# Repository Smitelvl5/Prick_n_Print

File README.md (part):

# Print-n-Prick

An IoT system that pairs a thermal receipt printer with a hand sanitizer dispenser, controlled remotely through an HTTP backend. Send messages from your phone and they print on thermal paper along with live weather and sensor data. A secondary display module provides a touchscreen GUI, web dashboard, and real-time sensor monitoring.

## HTTP backend

The TZT display polls your web server for commands, audio, and images. You run the included Flask server (or your own) and POST commands to it; the ESP32 polls `/api/commands`, `/api/audio`, and `/api/images`.

**Configure:** In **`include/config_tzt.h`** set **`BACKEND_URL`** to your server (e.g. `"http://192.168.1.100:5000"`). See [BACKEND_HTTP.md](BACKEND_HTTP.md) for setup and usage.

| What you send | What the TZT does |
|---------------|-------------------|
| **Text message** | Prints it (via Main ESP32), saves it to SD (`/data/messages/`), and shows it on the TZT screen. |
| **Audio** | Saves it to SD (`/data/audio/`) and plays it on the TZT. You can send a **URL** (TZT downloads and saves) or a **filename** (play a file already on SD). |
| **Image** | Saves it to SD (`/data/images/`) and shows it on the TZT. You can send a **URL** (TZT downloads and saves) or a **filename** (show a file already on SD). |

**Command types** (POST to your backend; see `raspberrypi/README.md` for the API):

- **`print`** – Text message (`type`, `data`, optional `source`)
- **`download_audio`** – Download audio from URL, save to SD, and play
- **`play_audio`** – Play a file already on SD
- **`download_image`** – Download image from URL, save to SD, and show
- **`show_image`** – Show a file already on SD

Pump/LED and other hardware control use the TZT’s web UI or HTTP API on port 8080.

---

## Architecture

The system is built on **two ESP32 modules** connected over ESP-NOW:

| | Main ESP32 (WROOM-32) | TZT Display ESP32 (CYD) |
|---|---|---|
| **Role** | Hardware controller | Brain / UI / cloud |
| **PlatformIO env** | `esp32-wroom-32` | `tzt-esp32-devkit` |
| **Serial port** | COM3 (CH340C on the main PCB) | COM7 (CH340) |
| **Controls** | Printer, pump, LED, sensors | 2.4" TFT + touch, web server, HTTP backend, SD card, speaker |
| **Network** | WiFi (for ESP-NOW channel sync) | WiFi + HTTP backend + HTTP server (port 8080) |
| **Config file** | `include/config.h` | `include/config_tzt.h` |

```
                 ┌──────────────────┐
  iOS Shortcut ──┤                  │
  Python script ─┤  HTTP backend    │
  Web UI (POST) ─┤  /api/commands   │
                 └────────┬─────────┘
                          │ poll (10-30 s)
                          ▼
              ┌──────────────────────────┐
              │   TZT Display ESP32     │
              │   (CYD 2.4" ILI9341)    │
              │                          │
              │  ● Web server :8080     │
              │  ● HTTP backend client  │
              │  ● LVGL touchscreen GUI │
              │  ● Reminder scheduler    │
              │  ● Grocery / Todo lists  │
              │  ● SD card (FAT32)       │
              │  ● Speaker (GPIO26 DAC)  │
              └────────────┬─────────────┘
                           │ ESP-NOW
                           ▼
              ┌──────────────────────────┐
              │   Main ESP32 (WROOM-32)  │
              │                          │
              │  ● Thermal printer       │
              │  ● Sanitizer pump        │
              │  ● 12 V LED (PWM)        │
              │  ● IR motion sensor      │
              │  ● Moisture sensor       │
              │  ● Light sensor (LM393)  │
              │  ● Sends sensor data     │
              │    back via ESP-NOW      │
              └──────────────────────────┘
```

### Message Flow

1. User sends message (iOS Shortcut, Python script, or web UI) to the HTTP backend
2. Message is POSTed to the backend (e.g. `/api/commands`)
3. TZT polls the backend every ~10–30 s, fetches new commands
4. TZT sends print command to Main ESP32 over ESP-NOW (chunked if > 199 bytes)
5. Main ESP32 assembles message, fetches weather, reads sensors, prints receipt
6. TZT marks the command as processed (backend may delete or mark it)

### Sensor Data Flow

1. Main ESP32 reads sensors every 2 seconds
2. Sends `SensorDataPacket` to TZT over ESP-NOW every 10 seconds
3. TZT updates the LVGL display and caches data for the web dashboard

---

## Quick Start

### Prerequisites

- [PlatformIO](https://platformio.org/) (CLI or VS Code extension)
- USB data cable for each ESP32
- HTTP backend server (see [BACKEND_HTTP.md](BACKEND_HTTP.md); optional for basic testing)

### 1. Set MAC Addresses

Each board prints its MAC address on boot over serial. Copy them into the config files:

- Main ESP32's MAC goes into TZT's own config, `include/config_tzt.h`, as `MAIN_ESP32_MAC_ADDRESS`
- TZT Display's MAC goes into Main's own config, `include/config.h`, as `TZT_DISPLAY_MAC_ADDRESS`

Format: `{0xAA, 0xBB, 0xCC, 0xDD, 0xEE, 0xFF}`

### 2. Build and Flash

```bash
# Main ESP32 (COM3)
pio run -e esp32-wroom-32 -t upload -t monitor

# TZT Display (COM7)
pio run -e tzt-esp32-devkit -t upload -t monitor
```

### 3. Connect to WiFi

On first boot each board creates a WiFi access point for configuration:

| Board | AP SSID | AP Password | Portal URL |
|---|---|---|---|
| Main ESP32 | `Print-n-Prick` | `your-portal-password` | `http://192.168.4.1` |
| TZT Display | `TZT_Display` | `your-portal-password` | `http://192.168.4.1` |

Connect to each AP, open the portal, and enter your home WiFi credentials. The boards save them and reconnect automatically on future boots.

### 4. Access the Web Dashboard

Once TZT is on your WiFi, find its IP in the serial monitor and open:

```
http://<TZT-IP>:8080
```

Password: `your-web-password` (set via `WEB_PASSWORD` in `secrets.h`)

---

## Hardware

### Main ESP32 (WROOM-32)

The Main ESP32 lives on a custom PCB (see [Main PCB](#main-pcb)) that replaces the old ESP32 DevKit, its breakout board and the separate LM2596 PSU board. The firmware pin map is unchanged.

#### Pin Map

| GPIO | Function | Direction | Component |
|------|----------|-----------|-----------|
| 2 | Status LED | Output | On-board LED D42 (active HIGH) |
| 16 | Serial RX2 | Input | Thermal printer data (J11), 1 k + clamp diode |
| 17 | Serial TX2 | Output | Thermal printer data (J11), 100 Ω series |
| 26 | Pump control | Output | AO3400A low-side MOSFET (J63) |
| 27 | LED PWM | Output | AO3400A low-side MOSFET, 12 V LED (J60) |
| 32 | IR sensor | Input | J12, 1 k + clamp to 3.3 V (sensor runs on 5 V) |
| 34 | Moisture sensor | ADC Input | J13, 1 k + 100 nF filter |
| 35 | Light sensor | ADC Input | J14, 1 k + 100 nF filter |

> GPIO 34 and 35 are input-only pins (no internal pull-ups). GPIO 16/17 are used for the thermal printer's Serial2 UART. GPIO 4, 13, 14, 18, 19, 21, 22, 23, 25 and 33 are spare and broken out on the J20 expansion header.

#### Components

| Device | Supply | Connector | Notes |
|---|---|---|---|
| **Thermal Printer** -- QR204 | 9 V (5-9 V), ~2 A peak | J61 power, J11 data | 9600 baud, Serial2. The firmware never reads from the printer, so leave the printer's TX wire (J11 pin 3) unconnected; on RS-232 models it swings negative. |
| **Sanitizer Pump** -- CJWP08 micro diaphragm | **3.3 V** | J63 | Voltage set by solder jumper JP1: bridge **1-2 for 3.3 V** (2-3 = 5 V would overdrive a 3.3 V pump). JP1 ships open. |
| **12 V LED** -- 5 W | 12 V, ~0.42 A | J60 | PWM dimming, software ramp (1 V/s), 1.1 A PTC |
| **IR Sensor** | **5 V** | J12 | Digital, active LOW = detected. Fed through its own 0.2 A PTC (F52); its output is clamped to 3.3 V before GPIO32 |
| **Moisture Sensor** -- capacitive | 3.3 V | J13 | Analog 0-4095 mapped to 0-100% |
| **Light Sensor** -- LM393 module | 3.3 V | J14 | Analog output, potentiometer for sensitivity tuning |
| **TZT Display** (CYD) | 5 V | J62 | 1.1 A PTC |

The moisture and light sensors share a 0.2 A PTC (F50) on 3.3 V, so their outputs can never exceed the ESP32's 3.3 V input limit.

### TZT Display ESP32 (CYD -- Cheap Yellow Display)

The TZT module is an [ESP32 Cheap Yellow Display](https://github.com/witnessmenow/ESP32-Cheap-Yellow-Display) -- a single board with an integrated 2.4" ILI9341 TFT, XPT2046 resistive touch controller, micro SD card slot, speaker amplifier, and RGB LED.

#### Pin Map (Fixed by PCB)

**Display (HSPI):**

| GPIO | Function |
|------|----------|
| 2 | TFT DC (data/command) |
| 12 | TFT MISO |
| 13 | TFT MOSI |
| 14 | TFT SCLK |
| 15 | TFT CS |
| 27 | TFT backlight |

**Touch (shared HSPI):**

| GPIO | Function |
|------|----------|
| 33 | XPT2046 CS |
| 25 | XPT2046 CLK |
| 32 | XPT2046 MOSI |
| 36 | XPT2046 IRQ |
| 39 | XPT2046 MISO |

**SD Card (VSPI):**

| GPIO | Function |
|------|----------|
| 5 | SD CS |
| 18 | SD SCK |
| 19 | SD MISO |
| 23 | SD MOSI |

**Peripherals:**

| GPIO | Function |
|------|----------|
| 4 | RGB LED -- Red |
| 16 | RGB LED -- Green |
| 17 | RGB LED -- Blue |
| 26 | Speaker (DAC channel 2, onboard amp) |
| 34 | LDR (light-dependent resistor) |

**Connectors:**

| Label | Type | Pins | Use |
|-------|------|------|-----|
| P1 | 4-pin 1.25 mm JST | VIN, TX, RX, GND | Serial |
| P3 | 4-pin 1.25 mm JST | GND, IO35, IO22, IO21 | GPIO |
| P4 | 2-pin 1.25 mm JST | Speaker +/- | Speaker output |
| CN1 | 4-pin 1.25 mm JST | GND, IO22, IO27, 3.3V | GPIO / I2C |

> Reference: [CYD Pin Documentation](https://github.com/witnessmenow/ESP32-Cheap-Yellow-Display/blob/main/PINS.md)

#### LVGL Screens

The touchscreen GUI has a bottom navigation bar with four tabs, plus a persistent status bar (time/IP/WiFi SSID):

1. **Home** -- latest printed message, quick status, and a button into message history (SD card)
2. **Sensors** -- live moisture, sanitizer, LED, and pump status from the Main ESP32 (read-only)
3. **Media** -- Photo/Audio sub-tab toggle: browse and play received images/audio, reminders, groceries, and todos
4. **Settings** -- WiFi SSID display, volume control, and device configuration

---

## ESP-NOW Protocol

The two boards communicate over ESP-NOW, a low-latency peer-to-peer protocol that works alongside WiFi.

### Packet Types

| Type | ID | Direction | Purpose |
|------|----|-----------|---------|
| `SENSOR_DATA` | 0x01 | Main -> TZT | Sensor readings (moisture, light, IR, LED, pump) |
| `COMMAND` | 0x02 | TZT -> Main | Hardware commands (print, pump, LED, settings) |
| `ACK` | 0x03 | Both | Acknowledgment with sequence number |
| `STATUS_REQUEST` | 0x04 | TZT -> Main | Request immediate sensor data |
| `CHUNK_ACK` | 0x05 | Main -> TZT | Acknowledge receipt of a print chunk |

### Command Types

| Command | ID | Description |
|---------|----|-------------|
| `CMD_PRINT` | 0x01 | Print message (up to 200 bytes) |
| `CMD_DISPENSE_START` | 0x02 | Start pump |
| `CMD_DISPENSE_STOP` | 0x03 | Stop pump |
| `CMD_RESET_SANITIZER` | 0x04 | Reset sanitizer level to 100% |
| `CMD_SET_LED_BRIGHTNESS` | 0x05 | Set LED (param1 = 0-255) |
| `CMD_SET_AUTO_BRIGHTNESS` | 0x07 | Toggle auto-brightness (param1 = 0/1) |
| `CMD_SET_AUTO_DISPENSE` | 0x0D | Toggle auto-dispense (param1 = 0/1) |
| `CMD_PRINT_CHUNK_START` | 0x10 | Begin chunked print (param2 = total chunks) |
| `CMD_PRINT_CHUNK` | 0x0F | One chunk of a long message (param1 = index) |

### Chunked Printing

Messages longer than 199 bytes are split into chunks:

1. TZT sends `CMD_PRINT_CHUNK_START` with the total chunk count
2. TZT sends the first `CMD_PRINT_CHUNK`
3. Main acknowledges with `CHUNK_ACK`
4. TZT sends the next chunk; repeat until done
5. Main assembles the full message and prints

Timeout: 15 seconds per chunk. Retry: 2 seconds. Max payload: ~25 KB (128 chunks x 199 bytes).

### Reliability

- XOR checksums on every packet
- Sequence numbers for ACK matching
- Automatic retry on send failure (2-3 attempts)
- Collision avoidance: 700 ms quiet period after receiving sensor data before sending commands
- Duplicate detection: Main deduplicates repeated settings commands within 1 second

---

## Web Dashboard

The TZT Display hosts a web server on port 8080 with a mobile-optimized dashboard.

### Authentication

- Password: `your-web-password` (set via `WEB_PASSWORD` in `secrets.h`)
- Session tokens valid for 1 hour (cookie-based)

### Sections

- **Sensor Status** -- Moisture, sanitizer level, light, IR, LED brightness, pump state (read-only; live data from the Main ESP32 over ESP-NOW)
- **Reminders** -- Schedule messages to print at a future time (presets: 1 min to 1 week)
- **Grocery List** -- Add items, print the list, clear all
- **Todo List** -- Add items, print the list, clear all
- **Hardware Diagnostics** -- Read sensors, send a test message through the full print pipeline (SD save -> ESP-NOW -> Main prints)

> Pump/LED testing and hardware settings (duration, cooldown, calibration, auto-dispense, auto-brightness) live only on the **Main ESP32's test server** (`http://<Main-ESP32-IP>:8081`) -- see [Hardware Testing](#hardware-testing) below. They used to be duplicated here and on the TZT, which let the two boards fight over settings on every TZT boot; now there's a single place that owns them.

### API Endpoints

| Method | Path | Description |
|--------|------|-------------|
| GET | `/api/login` | Shortcut-friendly login (session cookie) |
| GET | `/api/status` | Sensor readings |
| POST | `/api/reset-sanitizer` | Reset sanitizer to 100% |
| POST | `/api/test/send-message` | Send a test message through the full print pipeline |
| POST | `/api/test/play-audio` | Play an audio file already on SD |
| POST | `/api/test/show-image` | Show an image file already on SD |
| GET/POST | `/api/reminders` | List or add reminders |
| DELETE | `/api/reminders/{id}` | Delete a reminder |
| GET/POST | `/api/groceries` | List or add grocery items |
| DELETE | `/api/groceries` | Clear grocery list |
| POST | `/api/groceries/print` | Print grocery list |
| GET/POST | `/api/todos` | List or add todo items |
| DELETE | `/api/todos` | Clear todo list |
| POST | `/api/todos/print` | Print todo list |

Pump/LED/printer hardware control, tests, and settings are not on this server -- see [Hardware Testing](#hardware-testing) for the Main ESP32's own test server.

---

## Remote Messaging

### iOS Shortcuts

Create a shortcut with these four actions:

1. **Ask for Input** -- Question: "Your message:", type: Text, allow multiple lines
2. **Text** -- Paste the JSON template below, replacing the placeholder with the Provided Input variable:

```json
{
  "type": "print",
  "data": "[Provided Input]",
  "processed": false
}
```

3. **Get Contents of URL**
   - URL: `http://<YOUR-BACKEND-URL>/api/commands` (e.g. `http://192.168.1.100:5000/api/commands`)
   - Method: POST
   - Headers: `Content-Type: application/json`
   - Request Body: **File** (select the Text from step 2)

4. **Show Notification** -- "Message sent!"

> Use `"source": "web"` in the JSON to print the message alone (no header/weather). Omit `source` or use `"source": "shortcut"` for a full receipt with weather and sensor data.

### Python Script

```bash
python scripts/post_to_backend.py --url http://YOUR_SERVER_IP:5000 --message "Your message here"
```

### Print Formats

**Full receipt** (Shortcut / no source):

```
================================
     SMIT'S MESSAGE
================================
Date: Feb 17, 2026 02:30 PM

Your message text here

--------------------------------
Today's Weather:
  Partly Cloudy, 52 F

Moisture: 45.2%  Sanitizer: 78%
================================
```

**Message-only** (Web UI / `"source": "web"`):

```
Your message text here
```

---

## Hardware Testing

### Main ESP32 Test Server

The Main ESP32 runs an HTTP test server on **port 8081** (`http://<Main-ESP32-IP>:8081`) -- open it in a browser for a bench-test panel, or hit the routes directly with curl. This is the **only** place hardware is tested or reconfigured; the TZT dashboard's old duplicate controls (and its boot-time settings push over ESP-NOW) were removed so the two boards can no longer fight over pump/LED settings.

| Route | Description |
|-------|-------------|
| GET `/` | Bench-test web panel |
| GET `/status` | Live hardware status (JSON) |
| GET `/sensors` | Read moisture/IR/light now |
| GET `/printer/test` | Printer test pattern |
| GET `/printer/raw` | Raw test line |
| GET `/printer/receipt` | Sample receipt |
| GET `/printer/feed?lines=N` | Feed N lines |
| GET `/pump?ms=N` | Run pump for N ms (max 5000) |
| GET `/led?level=N&ms=N` | Set LED level (0-255) for N ms |
| GET `/settings` | Get pump duration/cooldown, auto-dispense, auto-brightness |
| GET `/settings/pump-duration?ms=N` | Set max pump dispense duration |
| GET `/settings/pump-cooldown?ms=N` | Set pump cooldown between dispenses |
| GET `/settings/auto-dispense?enabled=0\|1` | Toggle IR-sensor-triggers-pump |
| GET `/settings/auto-brightness?enabled=0\|1` | Toggle LED-follows-light-sensor |
| GET `/settings/light-calibration?point=min\|max` | Record current light reading as the dark/bright calibration point |

### TZT Display -- Touch Calibration

The current `TOUCH_AX`-`TOUCH_CY` coefficients in `config_tzt.h` were captured from a one-off calibration sketch that is no longer part of this repo. If the touchscreen needs recalibrating on different hardware, write a small sketch using `TFT_eSPI`'s built-in `calibrateTouch()` and paste the resulting coefficients into `config_tzt.h`.

---

## Project Structure

```
Prick_n_Print/
├── include/
│   ├── config.h              # Main ESP32 configuration (pins, timing, WiFi, ESP-NOW)
│   ├── config_tzt.h          # TZT Display configuration (display, WiFi, HTTP backend, ESP-NOW)
│   ├── User_Setup.h          # TFT_eSPI pin definitions (copied into library at build time)
│   ├── lv_conf.h             # LVGL configuration
│   ├── HardwareAbstraction.h # Hardware abstraction layer
│   ├── TestServer.h          # Bench-test HTTP server (port 8081) - hardware tests & settings
│   ├── PrinterService.h      # Thermal printer service
│   ├── HttpBackendService.h  # HTTP backend client
│   ├── ReminderService.h     # Reminder scheduler
│   └── Logger.h              # Serial logging
├── src/
│   ├── main.cpp              # Main ESP32 entry point
│   ├── HardwareAbstraction.cpp
│   ├── TestServer.cpp        # Bench-test HTTP server (port 8081) - hardware tests & settings
│   ├── PrinterService.cpp
│   ├── Logger.cpp
│   └── tzt-display/
│       └── main.cpp          # TZT Display entry point (web server, HTTP backend, LVGL, ESP-NOW)
├── raspberrypi/
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
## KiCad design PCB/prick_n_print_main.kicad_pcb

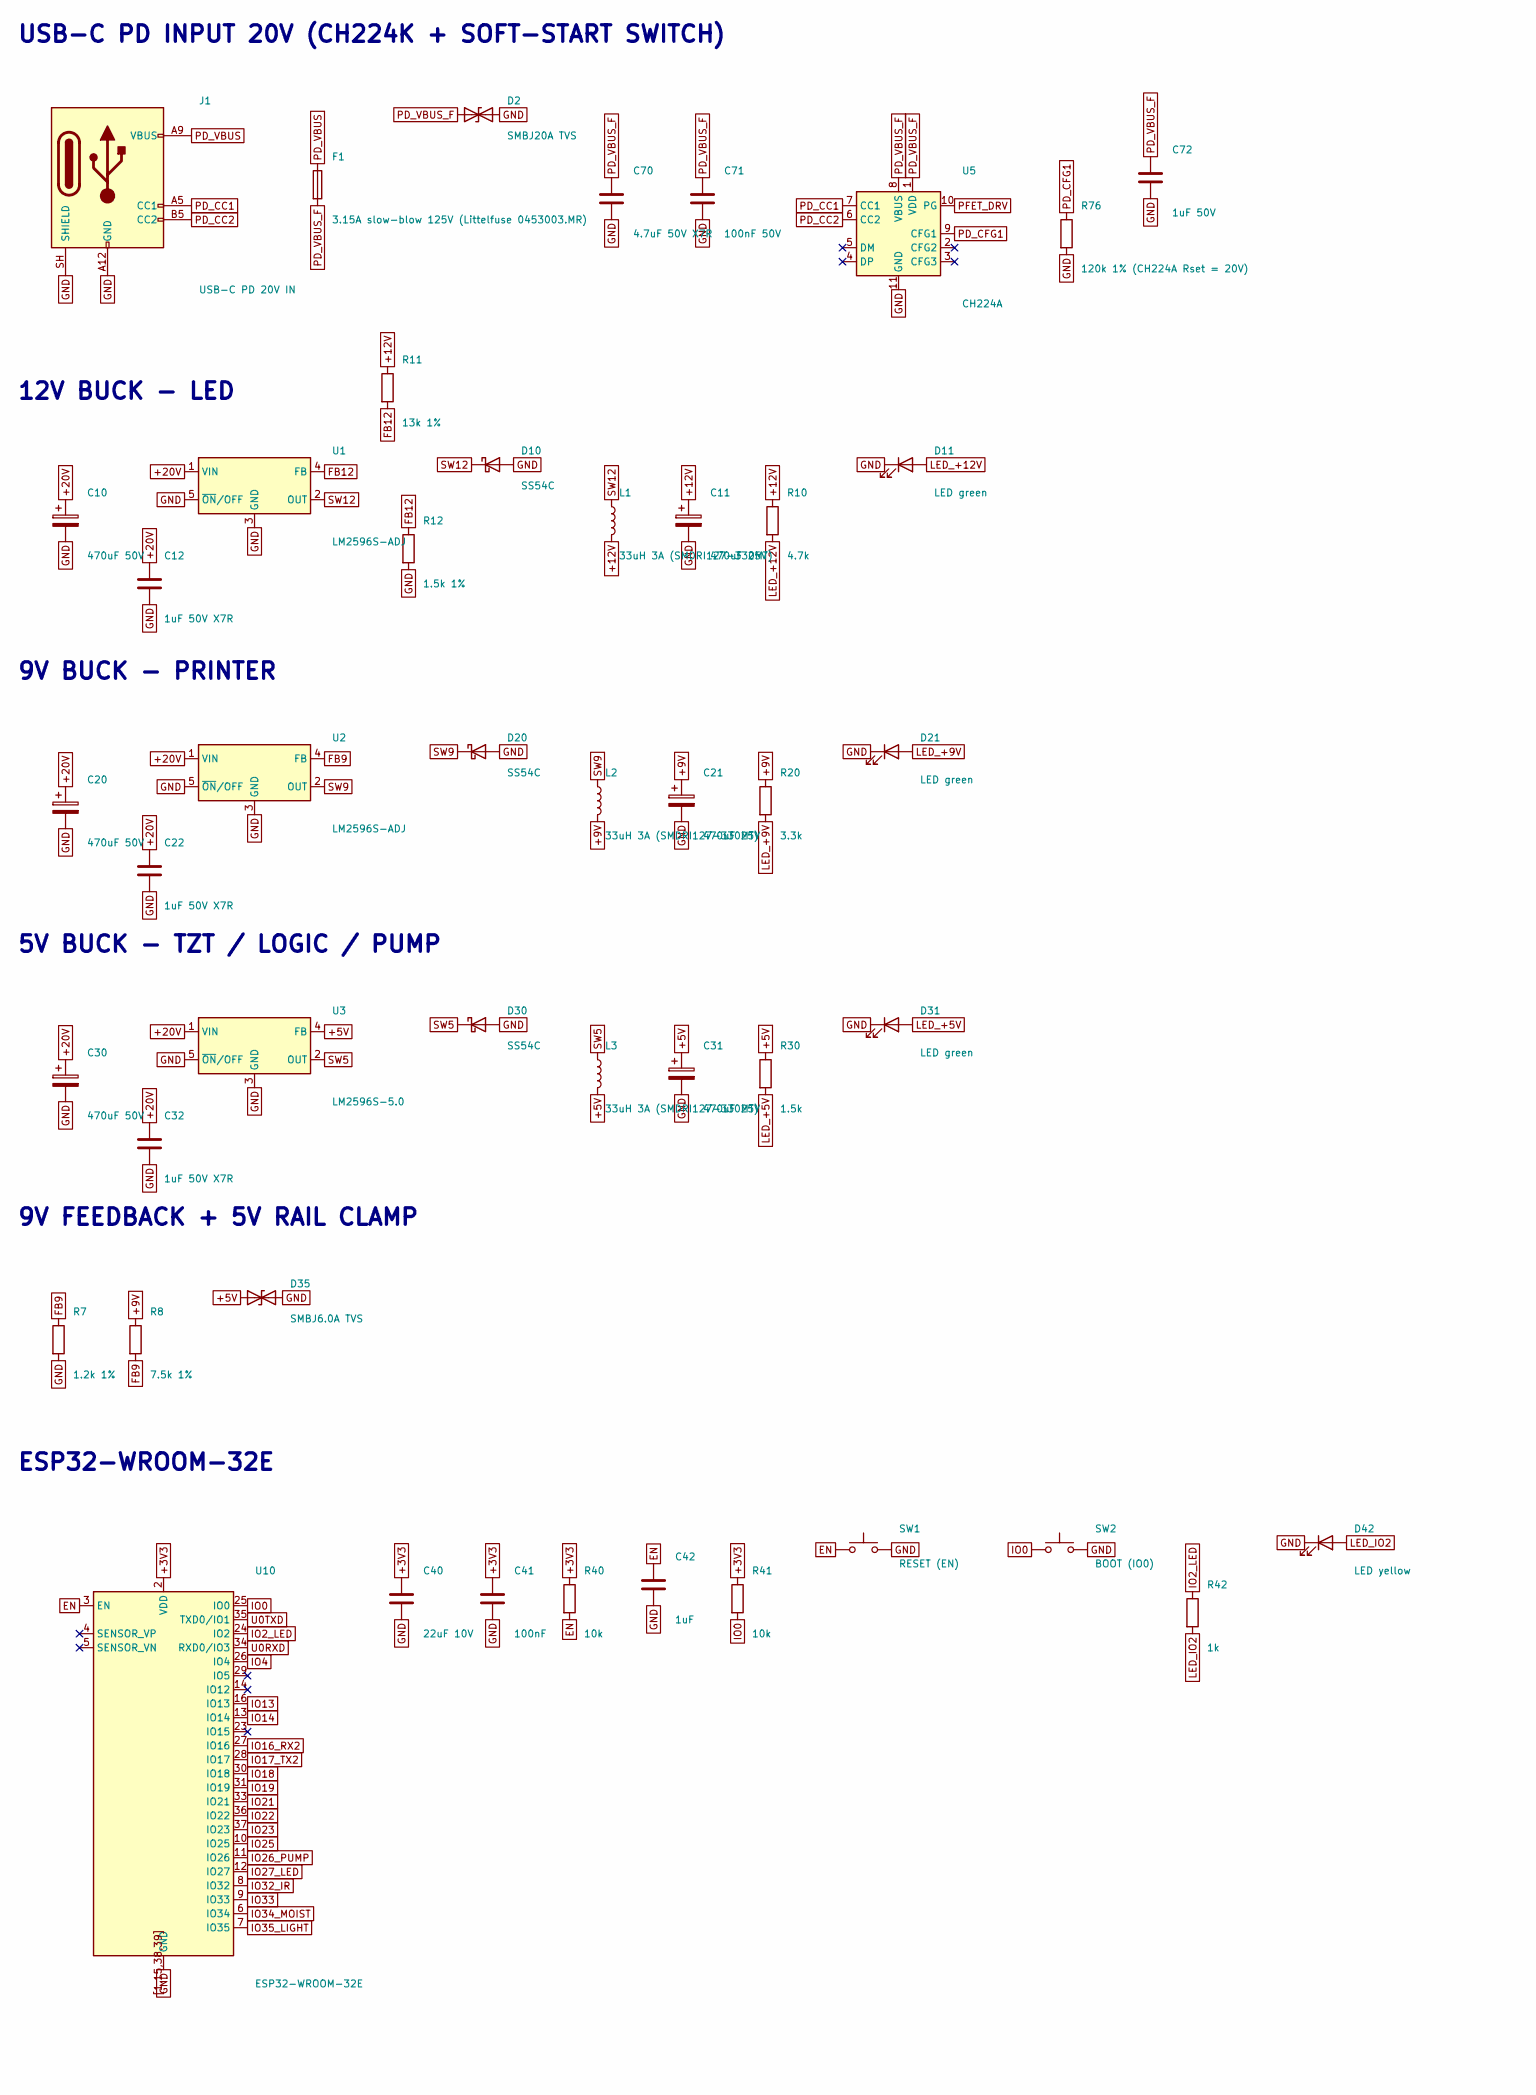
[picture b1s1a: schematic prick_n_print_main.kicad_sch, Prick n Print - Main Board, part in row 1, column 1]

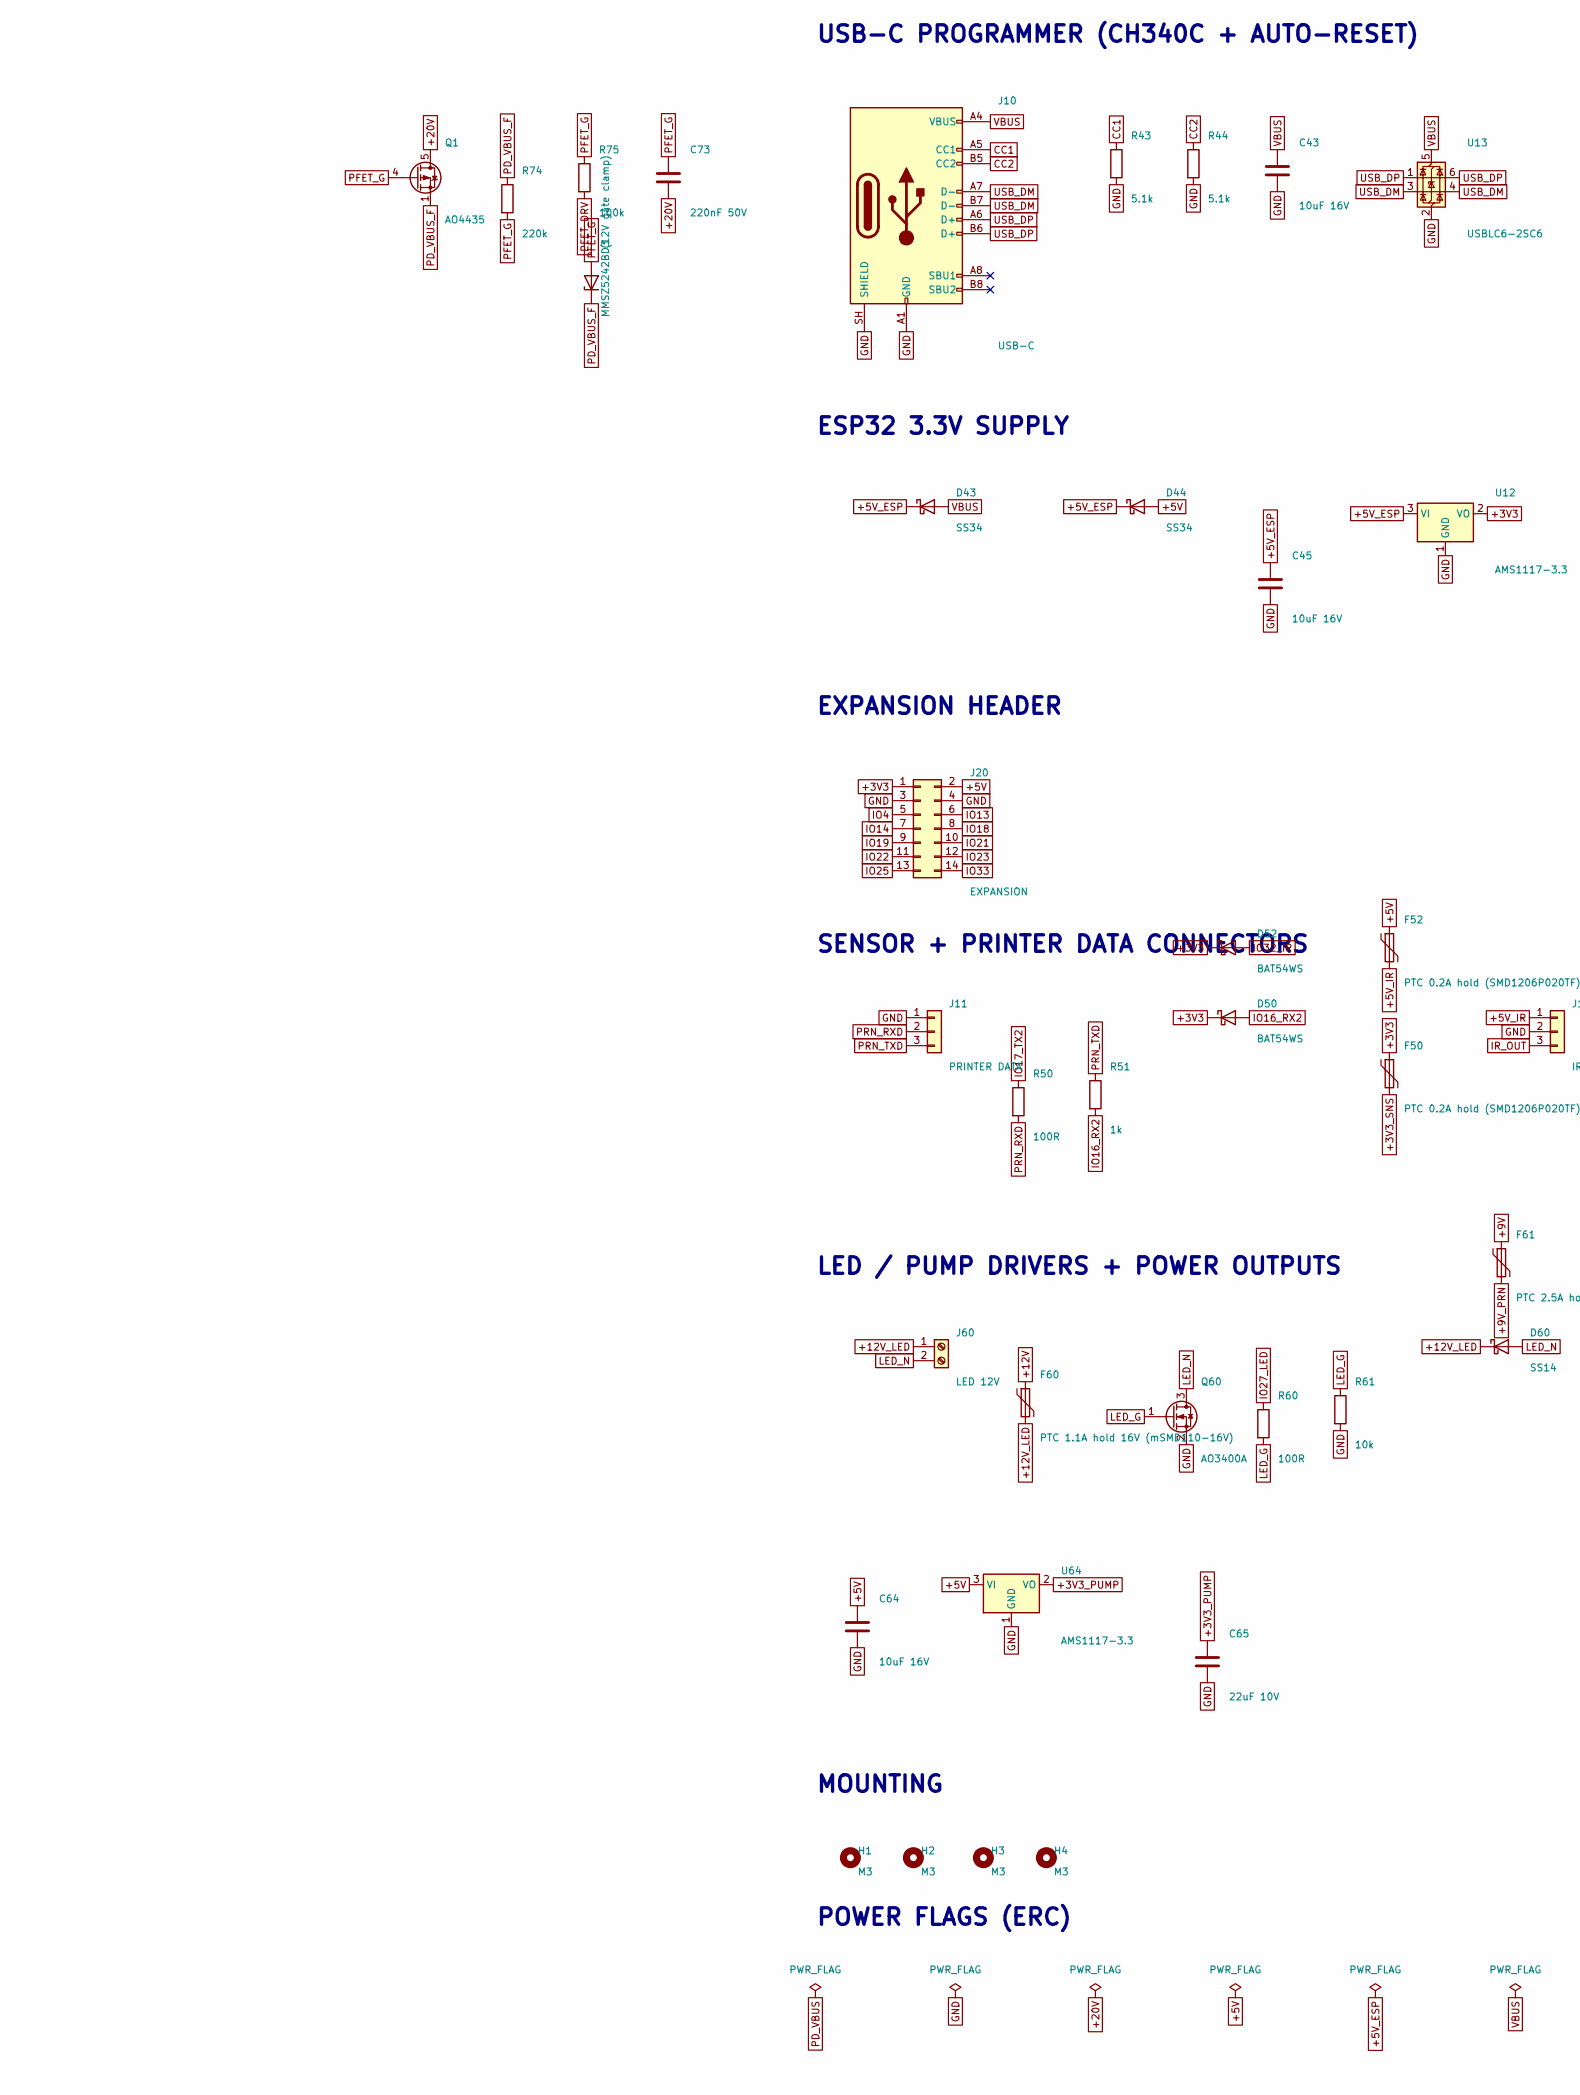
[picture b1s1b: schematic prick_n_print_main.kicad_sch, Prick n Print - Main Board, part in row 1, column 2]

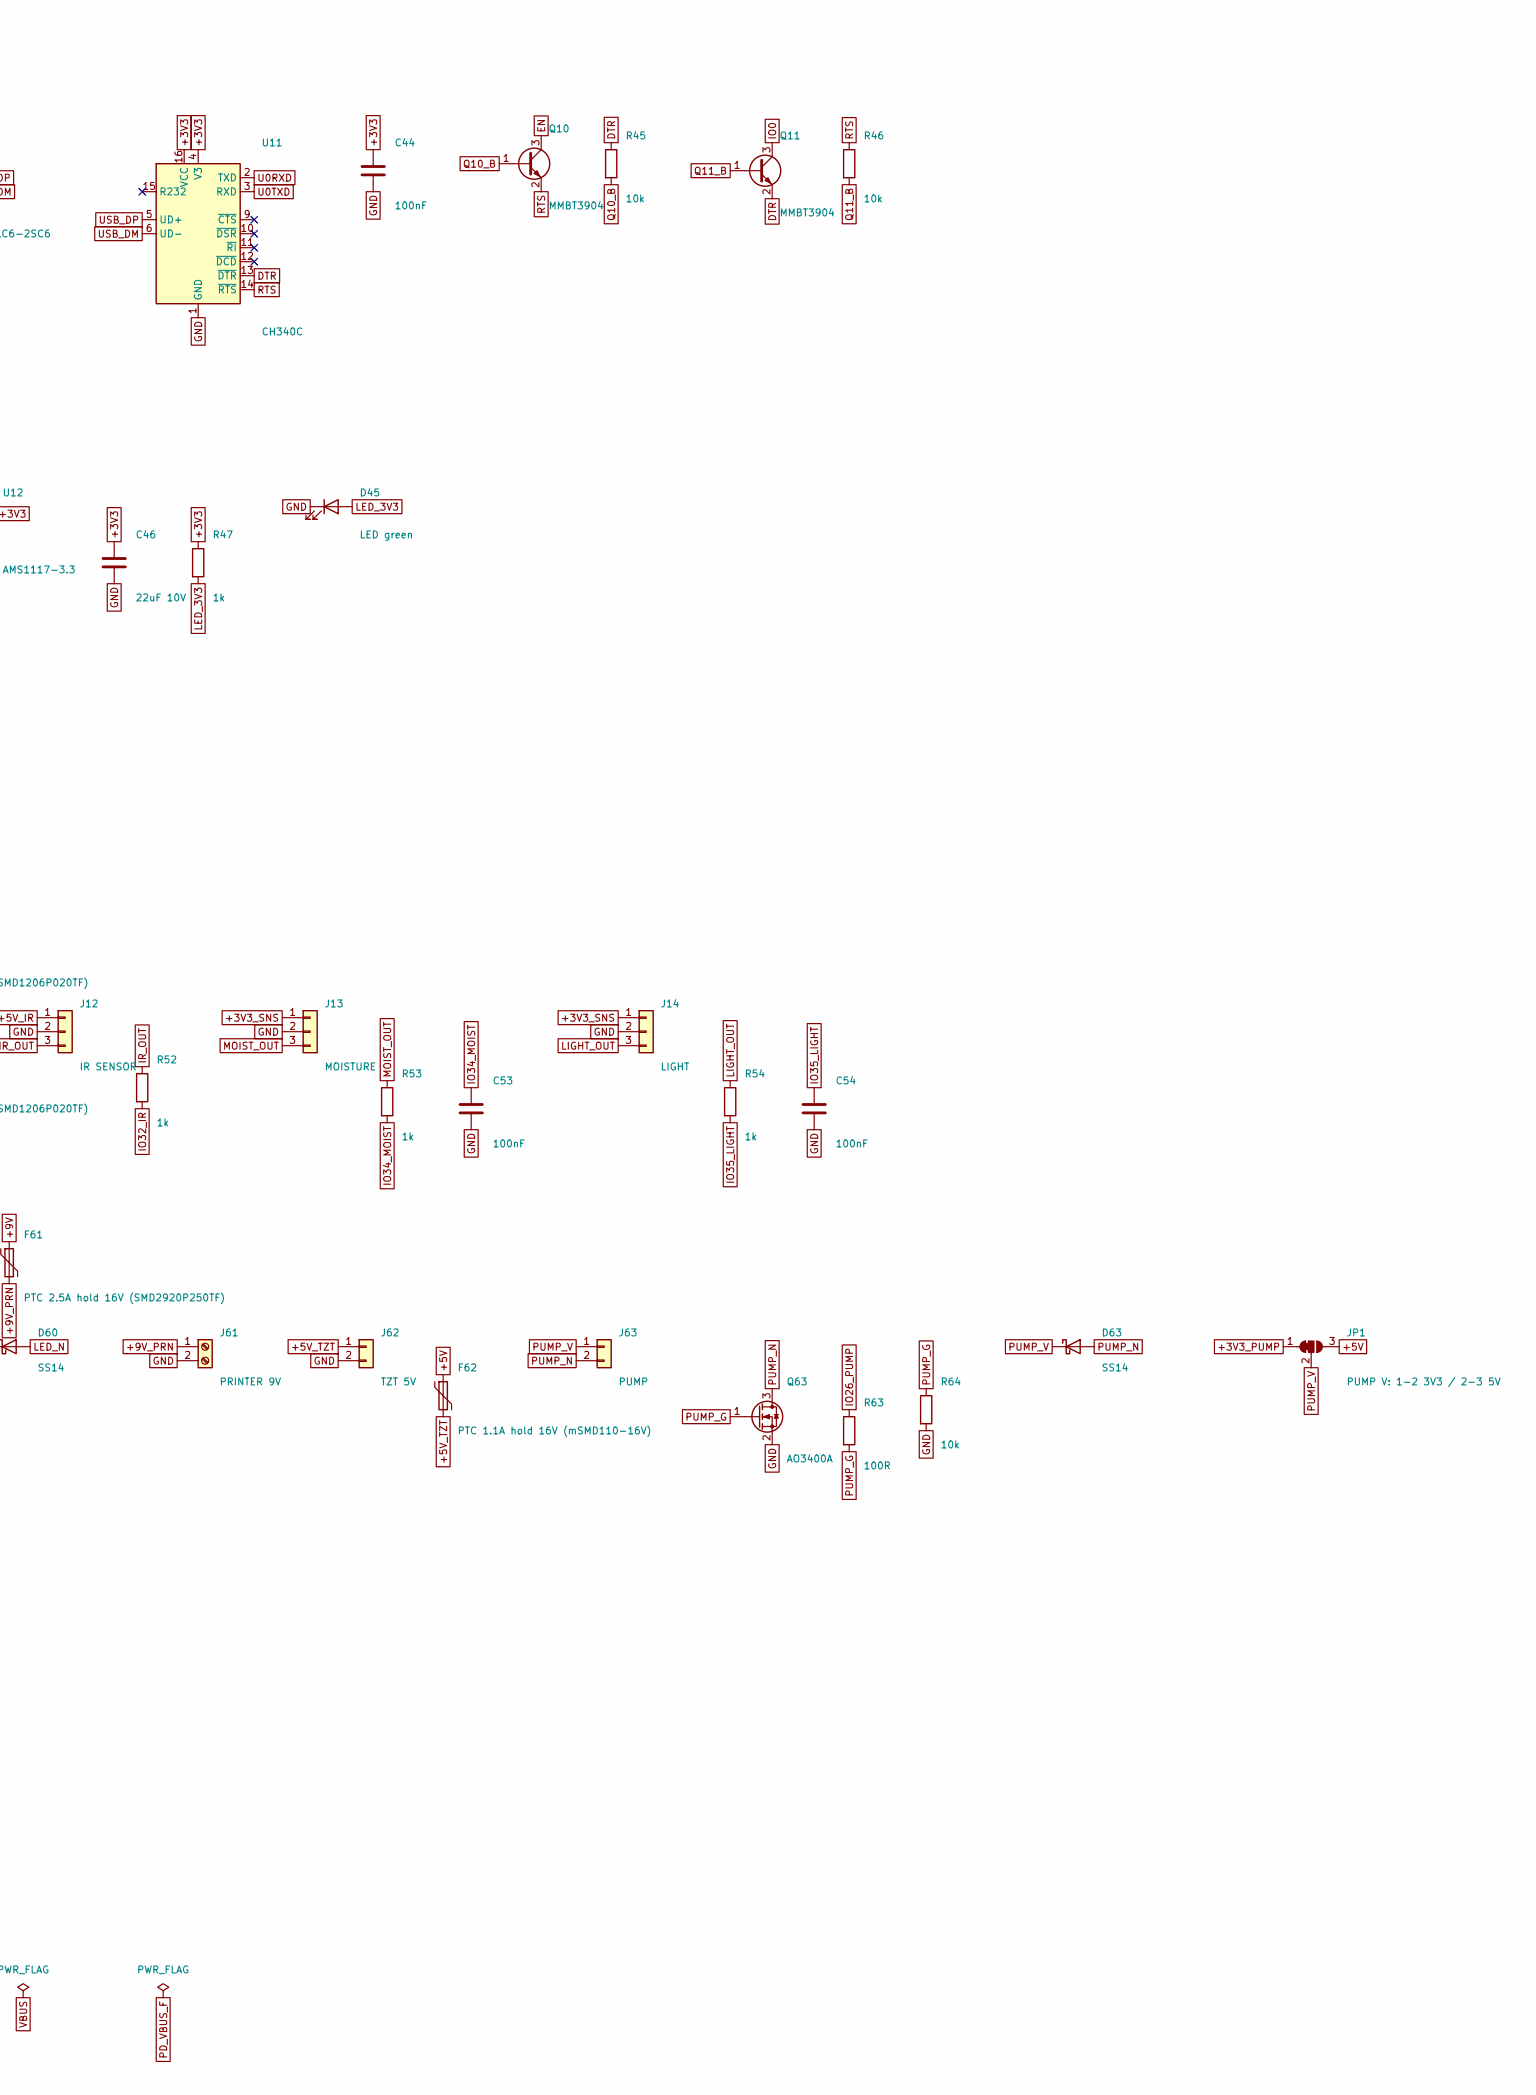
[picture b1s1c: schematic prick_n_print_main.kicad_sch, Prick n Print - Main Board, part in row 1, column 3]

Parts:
C10, C20, C30: 470uF 50V; CP_Radial_D12.5mm_P5.00mm; LCSC C2843292
C11, C21, C31: 470uF 25V; CP_Radial_D10.0mm_P5.00mm; LCSC C51018322
C12, C22, C32: 1uF 50V X7R; C_0805_2012Metric; LCSC C28323
C40, C46, C65: 22uF 10V; C_1206_3216Metric; LCSC C12891
C41, C44, C53, C54: 100nF; C_0805_2012Metric; LCSC C49678
C42: 1uF; C_0805_2012Metric; LCSC C28323
C43: 10uF 16V; C_0805_2012Metric; LCSC C15850
C45, C64: 10uF 16V; C_1206_3216Metric; LCSC C13585
C70: 4.7uF 50V X7R; C_1206_3216Metric; LCSC C29823
C71: 100nF 50V; C_0805_2012Metric; LCSC C49678
C72: 1uF 50V; C_0805_2012Metric; LCSC C28323
C73: 220nF 50V; C_0805_2012Metric; LCSC C5378
D2: SMBJ20A TVS; D_SMB; LCSC C19077575
D3: MMSZ5242B (12V gate clamp); D_SOD-123; LCSC C19077426
D10, D20, D30: SS54C; D_SMC; LCSC C18199188
D11, D21, D31, D45: LED green; LED_0805_2012Metric; LCSC C2297
D35: SMBJ6.0A TVS; D_SMB; LCSC C19077560
D42: LED yellow; LED_0805_2012Metric; LCSC C2296
D43, D44: SS34; D_SMA; LCSC C8678
D50, D52: BAT54WS; D_SOD-323; LCSC C7502694
D60, D63: SS14; D_SMA; LCSC C2480
F1: 3.15A slow-blow 125V (Littelfuse 0453003.MR); Fuse_Littelfuse-NANO2-451_453; LCSC C178991
F50, F52: PTC 0.2A hold (SMD1206P020TF); Fuse_1206_3216Metric; LCSC C20984
F60, F62: PTC 1.1A hold 16V (mSMD110-16V); Fuse_1812_4532Metric; LCSC C69691
F61: PTC 2.5A hold 16V (SMD2920P250TF); Fuse_2920_7451Metric; LCSC C20826
H1, H2, H3, H4: M3; MountingHole_3.2mm_M3
J1: USB-C PD 20V IN; USB_C_Receptacle_GCT_USB4125-xx-x_6P_TopMnt_Horizontal; LCSC C5246813
J10: USB-C; USB_C_Receptacle_HRO_TYPE-C-31-M-12; LCSC C165948
J11: PRINTER DATA; JST_XH_B3B-XH-A_1x03_P2.50mm_Vertical; LCSC C51940188
J12: IR SENSOR; JST_XH_B3B-XH-A_1x03_P2.50mm_Vertical; LCSC C51940188
J13: MOISTURE; JST_XH_B3B-XH-A_1x03_P2.50mm_Vertical; LCSC C51940188
J14: LIGHT; JST_XH_B3B-XH-A_1x03_P2.50mm_Vertical; LCSC C51940188
J20: EXPANSION; PinHeader_2x07_P2.54mm_Vertical; LCSC C71397
J60: LED 12V; TerminalBlock_Phoenix_MKDS-1,5-2_1x02_P5.00mm_Horizontal; LCSC C474950
J61: PRINTER 9V; TerminalBlock_Phoenix_MKDS-1,5-2_1x02_P5.00mm_Horizontal; LCSC C474950
J62: TZT 5V; JST_XH_B2B-XH-A_1x02_P2.50mm_Vertical; LCSC C265283
J63: PUMP; JST_XH_B2B-XH-A_1x02_P2.50mm_Vertical; LCSC C265283
JP1: PUMP V: 1-2 3V3 / 2-3 5V; SolderJumper-3_P1.3mm_Bridged12_RoundedPad1.0x1.5mm_NumberL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
L1, L2, L3: 33uH 3A (SMDRI127-330MT); L_12x12mm_H8mm; LCSC C9400
Q1: AO4435; SOIC-8_3.9x4.9mm_P1.27mm; LCSC C2944310
Q10, Q11: MMBT3904; SOT-23; LCSC C20526
Q60, Q63: AO3400A; SOT-23; LCSC C20917
R7: 1.2k 1%; R_0805_2012Metric; LCSC C17379
R8: 7.5k 1%; R_0805_2012Metric; LCSC C17807
R10: 4.7k; R_0805_2012Metric; LCSC C17673
R11: 13k 1%; R_0805_2012Metric; LCSC C17455
R12: 1.5k 1%; R_0805_2012Metric; LCSC C4310
R20: 3.3k; R_0805_2012Metric; LCSC C26010
R30: 1.5k; R_0805_2012Metric; LCSC C4310
R40, R41, R45, R46, R61, R64: 10k; R_0805_2012Metric; LCSC C17414
R42, R47, R51, R52, R53, R54: 1k; R_0805_2012Metric; LCSC C17513
R43, R44: 5.1k; R_0805_2012Metric; LCSC C27834
R50, R60, R63: 100R; R_0805_2012Metric; LCSC C17408
R74: 220k; R_0805_2012Metric; LCSC C17556
R75: 100k; R_0805_2012Metric; LCSC C149504
R76: 120k 1% (CH224A Rset = 20V); R_0805_2012Metric; LCSC C17436
SW1: RESET (EN); SW_SPST_TL3342; LCSC C318884
SW2: BOOT (IO0); SW_SPST_TL3342; LCSC C318884
U1, U2: LM2596S-ADJ; TO-263-5_TabPin3; LCSC C347423
U3: LM2596S-5.0; TO-263-5_TabPin3; LCSC C10002
U5: CH224A; SSOP-10-1EP_3.9x4.9mm_P1mm_EP2.1x3.3mm; LCSC C42459160
U10: ESP32-WROOM-32E; LCSC C701341
U11: CH340C; SOIC-16_3.9x9.9mm_P1.27mm; LCSC C84681
U12, U64: AMS1117-3.3; SOT-223-3_TabPin2; LCSC C6186
U13: USBLC6-2SC6; SOT-23-6; LCSC C7519

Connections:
+3V3: C40.1, C41.1, C44.1, C46.1, D50.1 (K), D52.1 (K), F50.1, J20.1, R40.1, R41.1, R47.1, U10.2 (VDD), U11.4 (V3), U11.16 (VCC), U12.2 (VO)
+3V3_PUMP: C65.1, JP1.1 (A), U64.2 (VO)
+3V3_SNS: F50.2, J13.1, J14.1
+5V: C31.1, C64.1, D35.1 (A1), D44.2 (A), F52.1, F62.1, J20.2, JP1.3 (B), L3.2, R30.1, U3.4 (FB), U64.3 (VI)
+5V_ESP: C45.1, D43.1 (K), D44.1 (K), U12.3 (VI)
+5V_IR: F52.2, J12.1
+5V_TZT: F62.2, J62.1
+9V: C21.1, F61.1, L2.2, R8.1, R20.1
+9V_PRN: F61.2, J61.1
+12V: C11.1, F60.1, L1.2, R10.1, R11.1
+12V_LED: D60.1 (K), F60.2, J60.1
+20V: C10.1, C12.1, C20.1, C22.1, C30.1, C32.1, C73.2, Q1.5 (D), Q1.6 (D), Q1.7 (D), Q1.8 (D), U1.1 (VIN), U2.1 (VIN), U3.1 (VIN)
CC1: J10.A5 (CC1), R43.1
CC2: J10.B5 (CC2), R44.1
DTR: Q11.2 (E), R45.1, U11.13 (~DTR)
EN: C42.1, Q10.3 (C), R40.2, SW1.1, U10.3 (EN)
FB9: R7.1, R8.2, U2.4 (FB)
FB12: R11.2, R12.1, U1.4 (FB)
GND: C10.2, C11.2, C12.2, C20.2, C21.2, C22.2, C30.2, C31.2, C32.2, C40.2, C41.2, C42.2, C43.2, C44.2, C45.2, C46.2, C53.2, C54.2, C64.2, C65.2, C70.2, C71.2, C72.2, D2.2 (A2), D10.2 (A), D11.1 (K), D20.2 (A), D21.1 (K), D30.2 (A), D31.1 (K), D35.2 (A2), D42.1 (K), D45.1 (K), J1.A12 (GND), J1.B12 (GND), J1.SH (SHIELD), J10.A1 (GND), J10.A12 (GND), J10.B1 (GND), J10.B12 (GND), J10.SH (SHIELD), J11.1, J12.2, J13.2, J14.2, J20.3, J20.4, J61.2, J62.2, Q60.2 (S), Q63.2 (S), R7.2, R12.2, R43.2, R44.2, R61.2, R64.2, R76.2, SW1.2, SW2.2, U1.3 (GND), U1.5 (~ON/OFF), U2.3 (GND), U2.5 (~ON/OFF), U3.3 (GND), U3.5 (~ON/OFF), U5.11 (GND), U10.1 (GND), U10.15 (GND), U10.38 (GND), U10.39 (GND), U10.[1,15,38,39] (GND), U11.1 (GND), U12.1 (GND), U13.2 (GND), U64.1 (GND)
IO0: Q11.3 (C), R41.2, SW2.1, U10.25 (IO0)
IO2_LED: R42.1, U10.24 (IO2)
IO4: J20.5, U10.26 (IO4)
IO13: J20.6, U10.16 (IO13)
IO14: J20.7, U10.13 (IO14)
IO16_RX2: D50.2 (A), R51.2, U10.27 (IO16)
IO17_TX2: R50.1, U10.28 (IO17)
IO18: J20.8, U10.30 (IO18)
IO19: J20.9, U10.31 (IO19)
IO21: J20.10, U10.33 (IO21)
IO22: J20.11, U10.36 (IO22)
IO23: J20.12, U10.37 (IO23)
IO25: J20.13, U10.10 (IO25)
IO26_PUMP: R63.1, U10.11 (IO26)
IO27_LED: R60.1, U10.12 (IO27)
IO32_IR: D52.2 (A), R52.2, U10.8 (IO32)
IO33: J20.14, U10.9 (IO33)
IO34_MOIST: C53.1, R53.2, U10.6 (IO34)
IO35_LIGHT: C54.1, R54.2, U10.7 (IO35)
IR_OUT: J12.3, R52.1
LED_3V3: D45.2 (A), R47.2
LED_+5V: D31.2 (A), R30.2
LED_+9V: D21.2 (A), R20.2
LED_+12V: D11.2 (A), R10.2
LED_G: Q60.1 (G), R60.2, R61.1
LED_IO2: D42.2 (A), R42.2
LED_N: D60.2 (A), J60.2, Q60.3 (D)
LIGHT_OUT: J14.3, R54.1
MOIST_OUT: J13.3, R53.1
PD_CC1: J1.A5 (CC1), U5.7 (CC1)
PD_CC2: J1.B5 (CC2), U5.6 (CC2)
PD_CFG1: R76.1, U5.9 (CFG1)
PD_VBUS: F1.1, J1.A9 (VBUS), J1.B9 (VBUS)
PD_VBUS_F: C70.1, C71.1, C72.1, D2.1 (A1), D3.1 (K), F1.2, Q1.1 (S), Q1.2 (S), Q1.3 (S), R74.1, U5.1 (VDD), U5.8 (VBUS)
PFET_DRV: R75.2, U5.10 (PG)
PFET_G: C73.1, D3.2 (A), Q1.4 (G), R74.2, R75.1
PRN_RXD: J11.2, R50.2
PRN_TXD: J11.3, R51.1
PUMP_G: Q63.1 (G), R63.2, R64.1
PUMP_N: D63.2 (A), J63.2, Q63.3 (D)
PUMP_V: D63.1 (K), J63.1, JP1.2 (C)
Q10_B: Q10.1 (B), R45.2
Q11_B: Q11.1 (B), R46.2
RTS: Q10.2 (E), R46.1, U11.14 (~RTS)
SW5: D30.1 (K), L3.1, U3.2 (OUT)
SW9: D20.1 (K), L2.1, U2.2 (OUT)
SW12: D10.1 (K), L1.1, U1.2 (OUT)
U0RXD: U10.34 (RXD0/IO3), U11.2 (TXD)
U0TXD: U10.35 (TXD0/IO1), U11.3 (RXD)
USB_DM: J10.A7 (D-), J10.B7 (D-), U11.6 (UD-), U13.3 (I/O2), U13.4 (I/O2)
USB_DP: J10.A6 (D+), J10.B6 (D+), U11.5 (UD+), U13.1 (I/O1), U13.6 (I/O1)
VBUS: C43.1, D43.2 (A), J10.A4 (VBUS), J10.A9 (VBUS), J10.B4 (VBUS), J10.B9 (VBUS), U13.5 (VBUS)

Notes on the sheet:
USB-C PD INPUT 20V (CH224K + SOFT-START SWITCH)
12V BUCK - LED
9V BUCK - PRINTER
5V BUCK - TZT / LOGIC / PUMP
9V FEEDBACK + 5V RAIL CLAMP
ESP32-WROOM-32E
USB-C PROGRAMMER (CH340C + AUTO-RESET)
ESP32 3.3V SUPPLY
EXPANSION HEADER
SENSOR + PRINTER DATA CONNECTORS
LED / PUMP DRIVERS + POWER OUTPUTS
MOUNTING
POWER FLAGS (ERC)

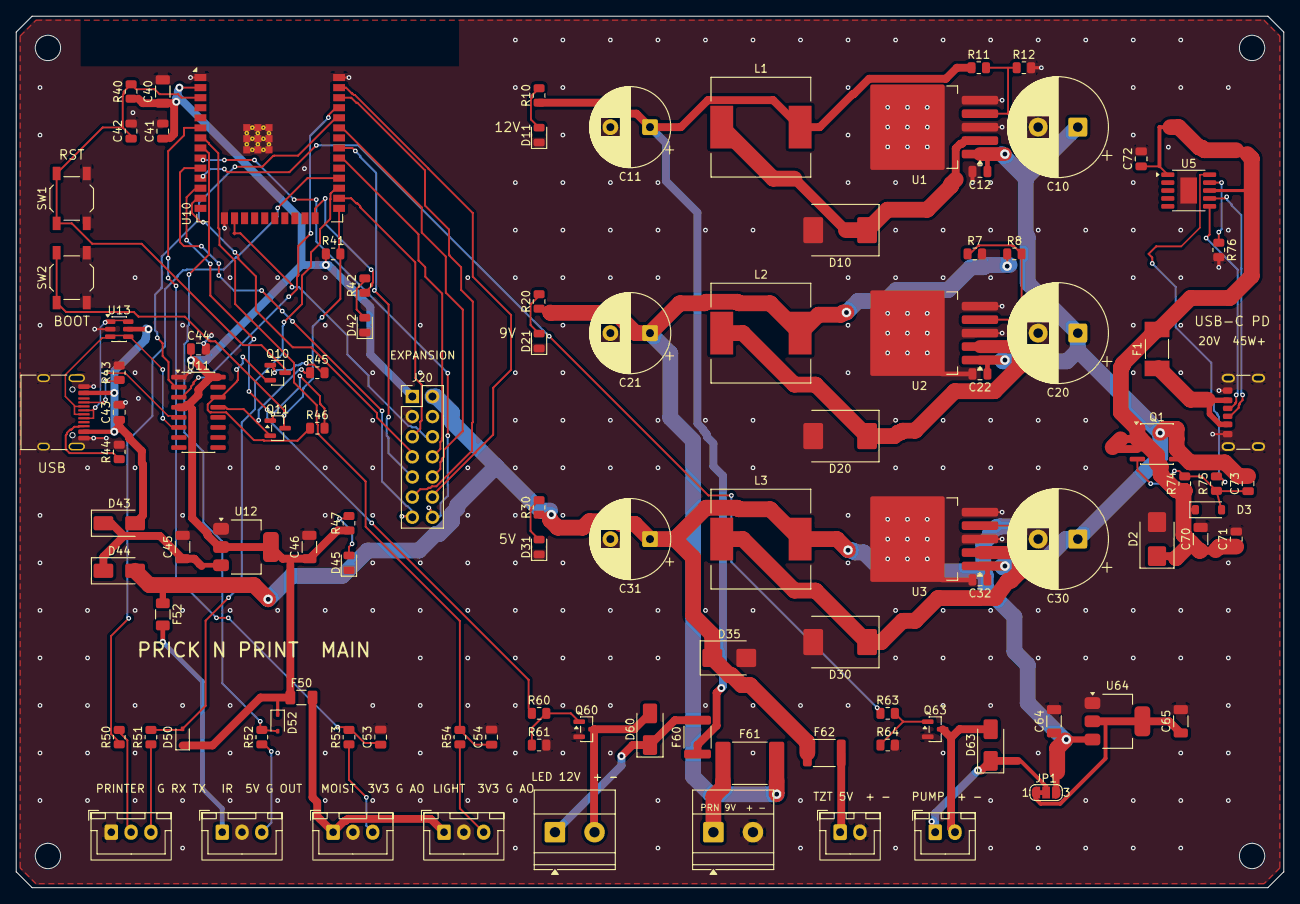
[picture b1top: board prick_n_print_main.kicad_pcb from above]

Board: 2 copper layers, 160.0 x 110.0 mm, 109 parts (0 on the bottom side), 71 nets.

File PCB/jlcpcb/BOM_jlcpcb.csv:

Comment,Designator,Footprint,LCSC Part #
1uF 50V X7R,"C12,C22,C32",C_0805_2012Metric,C28323
22uF 10V,"C40,C46,C65",C_1206_3216Metric,C12891
100nF,"C41,C44,C53,C54",C_0805_2012Metric,C49678
1uF,C42,C_0805_2012Metric,C28323
10uF 16V,C43,C_0805_2012Metric,C15850
10uF 16V,"C45,C64",C_1206_3216Metric,C13585
4.7uF 50V X7R,C70,C_1206_3216Metric,C29823
100nF 50V,C71,C_0805_2012Metric,C49678
1uF 50V,C72,C_0805_2012Metric,C28323
220nF 50V,C73,C_0805_2012Metric,C5378
SMBJ20A TVS,D2,D_SMB,C19077575
MMSZ5242B (12V gate clamp),D3,D_SOD-123,C19077426
SS54C,"D10,D20,D30",D_SMC,C18199188
LED green,"D11,D21,D31,D45",LED_0805_2012Metric,C2297
SMBJ6.0A TVS,D35,D_SMB,C19077560
LED yellow,D42,LED_0805_2012Metric,C2296
SS34,"D43,D44",D_SMA,C8678
BAT54WS,"D50,D52",D_SOD-323,C7502694
SS14,"D60,D63",D_SMA,C2480
3.15A slow-blow 125V (Littelfuse 0453003.MR),F1,Fuse_Littelfuse-NANO2-451_453,C178991
PTC 0.2A hold (SMD1206P020TF),"F50,F52",Fuse_1206_3216Metric,C20984
PTC 1.1A hold 16V (mSMD110-16V),"F60,F62",Fuse_1812_4532Metric,C69691
PTC 2.5A hold 16V (SMD2920P250TF),F61,Fuse_2920_7451Metric,C20826
USB-C PD 20V IN,J1,USB_C_Receptacle_GCT_USB4125-xx-x_6P_TopMnt_Horizontal,C5246813
USB-C,J10,USB_C_Receptacle_HRO_TYPE-C-31-M-12,C165948
33uH 3A (SMDRI127-330MT),"L1,L2,L3",L_12x12mm_H8mm,C9400
AO4435,Q1,SOIC-8_3.9x4.9mm_P1.27mm,C2944310
MMBT3904,"Q10,Q11",SOT-23,C20526
AO3400A,"Q60,Q63",SOT-23,C20917
1.2k 1%,R7,R_0805_2012Metric,C17379
7.5k 1%,R8,R_0805_2012Metric,C17807
4.7k,R10,R_0805_2012Metric,C17673
13k 1%,R11,R_0805_2012Metric,C17455
1.5k 1%,R12,R_0805_2012Metric,C4310
3.3k,R20,R_0805_2012Metric,C26010
1.5k,R30,R_0805_2012Metric,C4310
10k,"R40,R41,R45,R46,R61,R64",R_0805_2012Metric,C17414
1k,"R42,R47,R51,R52,R53,R54",R_0805_2012Metric,C17513
5.1k,"R43,R44",R_0805_2012Metric,C27834
100R,"R50,R60,R63",R_0805_2012Metric,C17408
220k,R74,R_0805_2012Metric,C17556
100k,R75,R_0805_2012Metric,C149504
120k 1% (CH224A Rset = 20V),R76,R_0805_2012Metric,C17436
RESET (EN),SW1,SW_SPST_TL3342,C318884
BOOT (IO0),SW2,SW_SPST_TL3342,C318884
LM2596S-ADJ,"U1,U2",TO-263-5_TabPin3,C347423
LM2596S-5.0,U3,TO-263-5_TabPin3,C10002
CH224A,U5,SSOP-10-1EP_3.9x4.9mm_P1mm_EP2.1x3.3mm,C42459160
ESP32-WROOM-32E,U10,ESP32-WROOM-32E,C701341
CH340C,U11,SOIC-16_3.9x9.9mm_P1.27mm,C84681
AMS1117-3.3,"U12,U64",SOT-223-3_TabPin2,C6186
USBLC6-2SC6,U13,SOT-23-6,C7519

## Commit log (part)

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2025-12-27 Rename project to Print_n_Prick throughout codebase
    Replaced all references to 'Printer Pot' with 'Print_n_Prick' in documentation, HTML, configuration, versioning, Python scripts, and C++ source files. Updated WiFi SSID, web interface titles, OTA ser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
2026-01-08 Add light sensor and LED PWM brightness control
    Integrated LM393 light sensor support and 12V LED PWM brightness control via MOSFET. LED brightness is now automatically adjusted inversely to ambient light level. Updated hardware abstraction, confi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
2026-01-21 yuiyui
    huiyhui
2026-02-03 qweqwe
    chnages
2026-02-25 sdf
    d
2026-02-27 Add Raspberry Pi Flask server and tooling
    Add a Raspberry Pi backend: a Flask app (raspberrypi/app.py) providing an ESP32-compatible HTTP API and a web UI (templates/index.html). Include setup and management tooling (setup.sh, set-http-passw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
